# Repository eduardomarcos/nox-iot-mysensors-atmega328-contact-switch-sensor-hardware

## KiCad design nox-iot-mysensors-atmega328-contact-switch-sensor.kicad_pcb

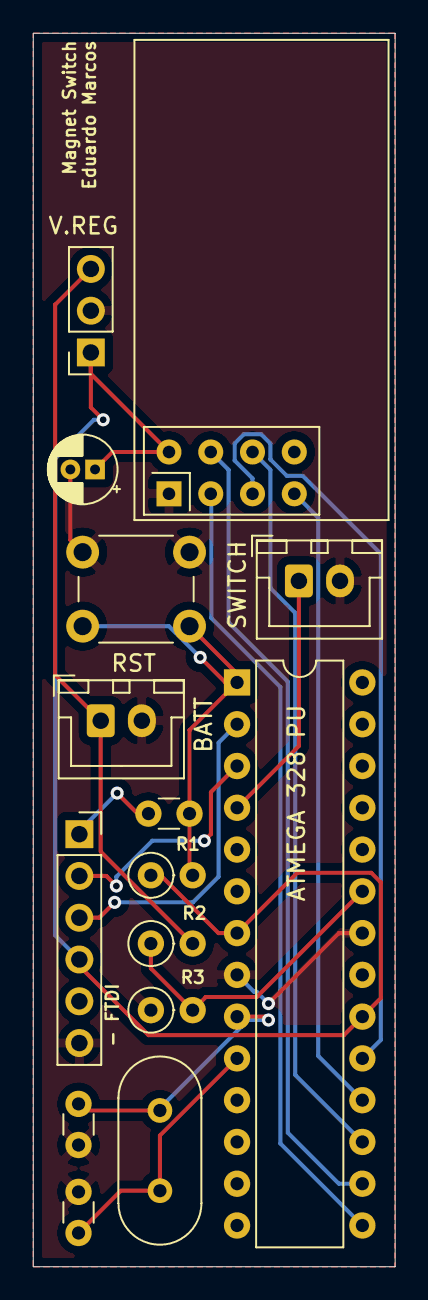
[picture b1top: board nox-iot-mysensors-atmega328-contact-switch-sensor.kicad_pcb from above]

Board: 2 copper layers, 22.0 x 75.0 mm, 15 parts (0 on the bottom side), 16 nets.

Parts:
- FTDI: FTDI; PinSocket_1x06_P2.54mm_Vertical
ATMEGA 328 PU: ATmega328-PU; DIP-28_W7.62mm
BATT: Battery Connection; JST_XH_B2B-XH-A_1x02_P2.50mm_Vertical
C1, C2: 22pF; C_Disc_D3.0mm_W1.6mm_P2.50mm
C3: 10uF; CP_Radial_D4.0mm_P1.50mm
C4: 100 nF; C_Disc_D3.0mm_W1.6mm_P2.50mm
R1: 10K; R_Axial_DIN0207_L6.3mm_D2.5mm_P2.54mm_Vertical
R2: 1M; R_Axial_DIN0207_L6.3mm_D2.5mm_P2.54mm_Vertical
R3: 430K; R_Axial_DIN0207_L6.3mm_D2.5mm_P2.54mm_Vertical
RST: SW_Push; SW_PUSH_6mm
SWITCH: Magnet Switch; JST_XH_B2B-XH-A_1x02_P2.50mm_Vertical
U3: NRF24L01; nRF24L01_Breakout
V.REG: WAVGAT 3.3V; PinSocket_1x03_P2.54mm_Vertical
Y1: 16Mhz; Crystal_HC49-4H_Vertical

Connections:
+3V3: - FTDI.4, ATMEGA 328 PU.7, ATMEGA 328 PU.20, C3.1, R1.1, U3.2, V.REG.1
+BATT: BATT.1, R2.2, V.REG.3
/BATT_SENSOR: ATMEGA 328 PU.23, R2.1, R3.2
/CE: ATMEGA 328 PU.15, U3.3
/CNS: ATMEGA 328 PU.16, U3.4
/MAGNET_IN: ATMEGA 328 PU.4, SWITCH.1
/MISO: ATMEGA 328 PU.18, U3.7
/MOSI: ATMEGA 328 PU.17, U3.6
/RST: ATMEGA 328 PU.1, C4.2, R1.2, RST.1
/RX: - FTDI.2, ATMEGA 328 PU.3
/SCK: ATMEGA 328 PU.19, U3.5
/TX: - FTDI.3, ATMEGA 328 PU.2
GND: - FTDI.6, ATMEGA 328 PU.8, ATMEGA 328 PU.22, BATT.2, C1.1, C2.1, C3.2, R3.1, RST.2, SWITCH.2, U3.1, V.REG.2
unnamed: ATMEGA 328 PU.9, C1.2, Y1.1
unnamed: ATMEGA 328 PU.10, C2.2, Y1.2
unnamed: - FTDI.1, C4.1

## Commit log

2021-04-24 init commit
2021-04-24 voltage divider for battery sensor
2021-04-25 updated with voltage divider value
